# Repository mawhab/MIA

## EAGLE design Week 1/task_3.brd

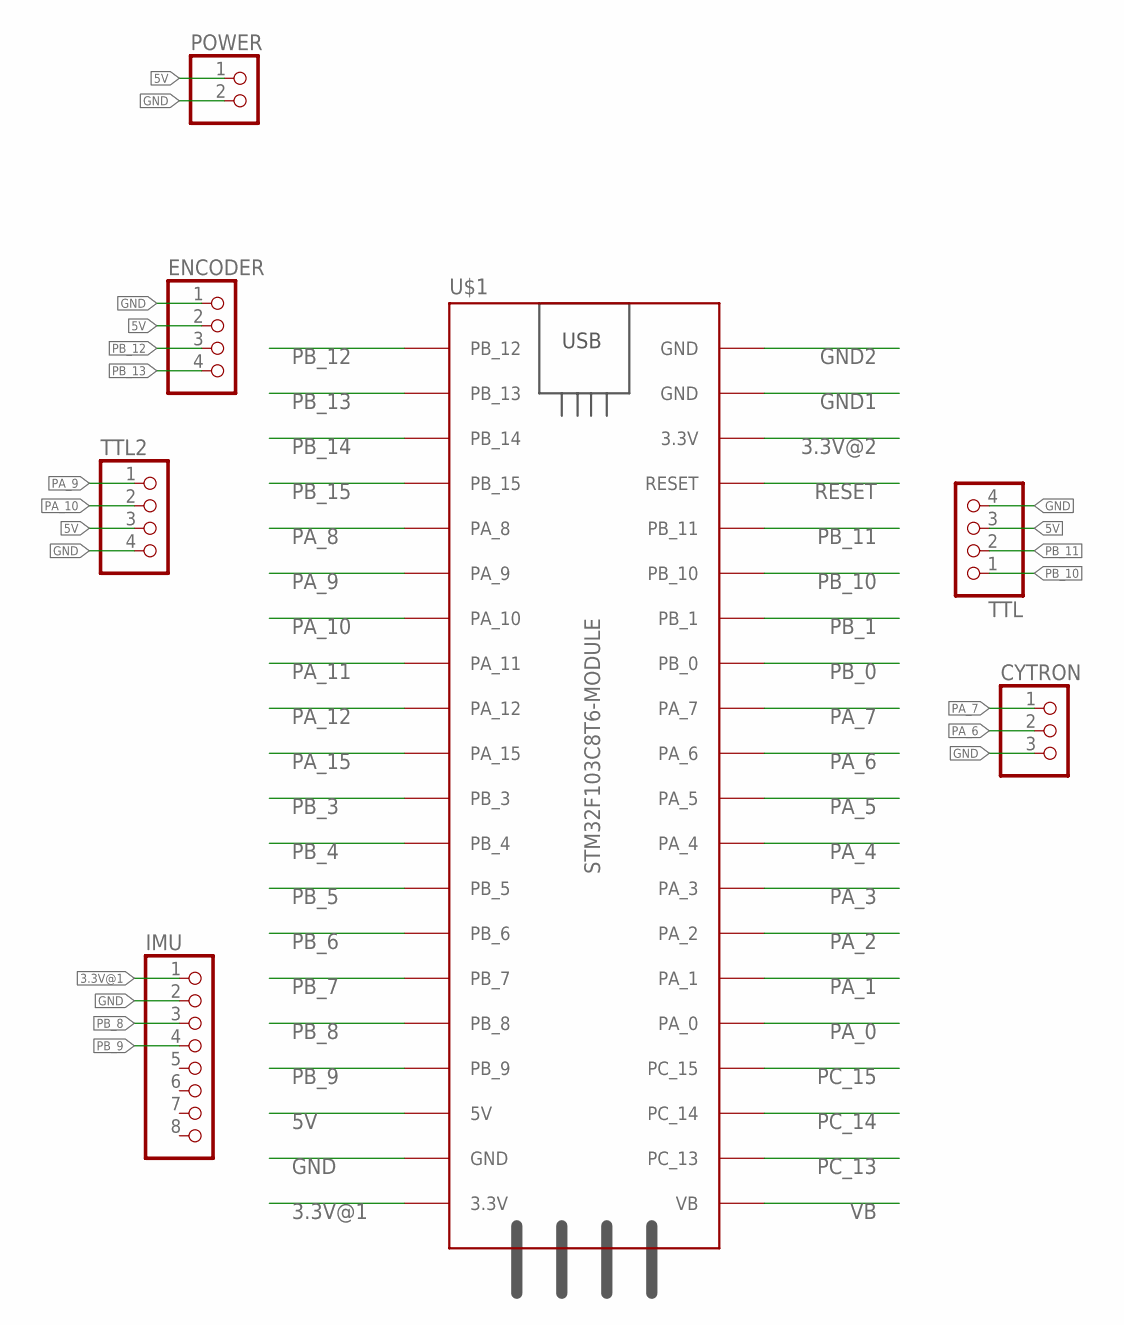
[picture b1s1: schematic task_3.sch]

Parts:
CYTRON: PINHD-3_DATA; 1X03_DATA
ENCODER: PINHD-4_DATA; 1X04_DATA
IMU: PINHD-1X8; 1X08
POWER: PINHD-2_DATA; 1X02_DATA
TTL, TTL2: PINHD-4_DATA; 1X04_DATA
U$1: STM32F103C8T6-MODULE

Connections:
3.3V@1: IMU.1, U$1.3.3V_1 (3.3V)
3.3V@2: U$1.3.3V_2 (3.3V)
5V: ENCODER.2, POWER.1, TTL.3, TTL2.3, U$1.5V
GND: CYTRON.3, ENCODER.1, IMU.2, POWER.2, TTL.4, TTL2.4, U$1.GND_1 (GND)
GND1: U$1.GND_2 (GND)
GND2: U$1.GND_3 (GND)
PA_0: U$1.PA_0
PA_1: U$1.PA_1
PA_2: U$1.PA_2
PA_3: U$1.PA_3
PA_4: U$1.PA_4
PA_5: U$1.PA_5
PA_6: CYTRON.2, U$1.PA_6
PA_7: CYTRON.1, U$1.PA_7
PA_8: U$1.PA_8
PA_9: TTL2.1, U$1.PA_9
PA_10: TTL2.2, U$1.PA_10
PA_11: U$1.PA_11
PA_12: U$1.PA_12
PA_15: U$1.PA_15
PB_0: U$1.PB_0
PB_1: U$1.PB_1
PB_3: U$1.PB_3
PB_4: U$1.PB_4
PB_5: U$1.PB_5
PB_6: U$1.PB_6
PB_7: U$1.PB_7
PB_8: IMU.3, U$1.PB_8
PB_9: IMU.4, U$1.PB_9
PB_10: TTL.1, U$1.PB_10
PB_11: TTL.2, U$1.PB_11
PB_12: ENCODER.3, U$1.PB_12
PB_13: ENCODER.4, U$1.PB_13
PB_14: U$1.PB_14
PB_15: U$1.PB_15
PC_13: U$1.PC_13
PC_14: U$1.PC_14
PC_15: U$1.PC_15
RESET: U$1.RESET
VB: U$1.VB

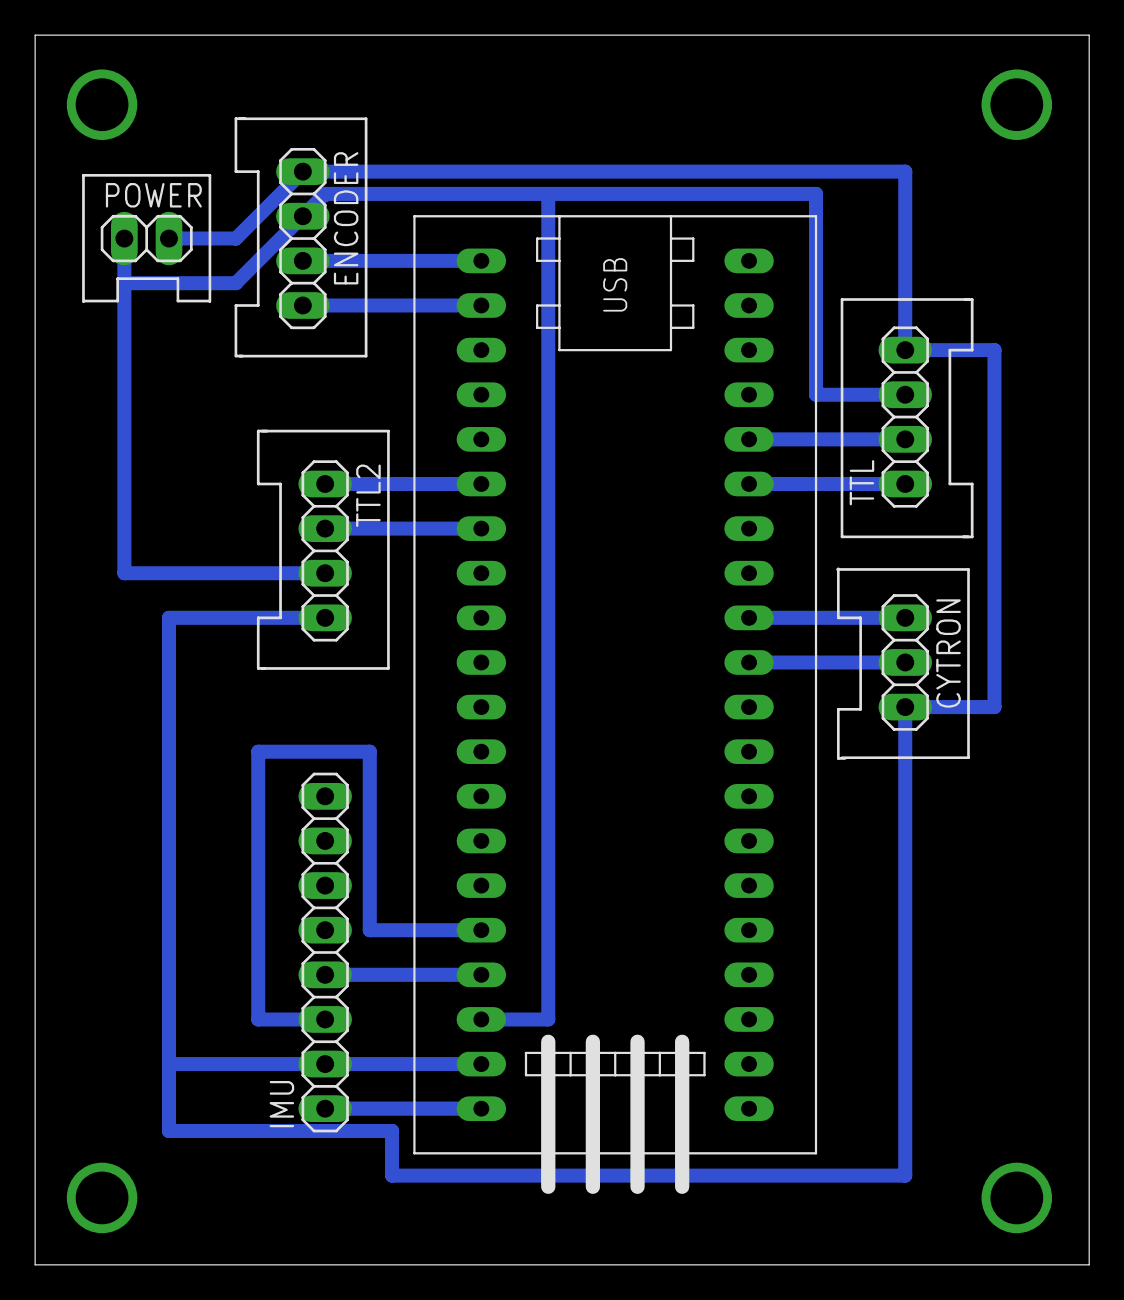
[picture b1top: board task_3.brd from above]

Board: 2 copper layers, 60.0 x 70.0 mm, 7 parts (0 on the bottom side), 13 nets.

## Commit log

2021-10-26 Task 1 done
2021-10-27 added second ttl and used correct data pinheads
2021-10-30 fixed pin configuration and routing errors, and also updated dimensions and added vias
2021-10-30 fixed minor error
2021-11-01 ommitted use of jumpers
2021-11-01 Finished task 1 of week 2
2021-11-02 Finished task 2 week 2
2021-11-05 Tested in workshop, changed some lines
2021-11-08 Created new git branch and finished week 3 task
2021-11-08 added filter for feedback speed
2021-11-11 tried at workshop, made lots of changes, removed many functions
2021-11-16 Finished week 4 tasks, need some small modifications
